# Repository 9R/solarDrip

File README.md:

# SolarDrip

Aim of this project is to create a drop in replacement PCB for low cost solar irrigation systems to allow integration into home automation setups like home-assistant.

## Features

  * solar and usb-c charging
  * basic battery management
  * pump control
  * 2 capacitative sensors (soil & water level)
  * i2c available for additional actors or sensors
  * spare GPIOs

## Hardware

The PCB fits this [solar irrigation system](https://www.aliexpress.com/item/1005006386588305.html). Other, similar systems might be compatible as well. Connecting a pump, 18650 battery and a big enough 6V solar panel should be enough.

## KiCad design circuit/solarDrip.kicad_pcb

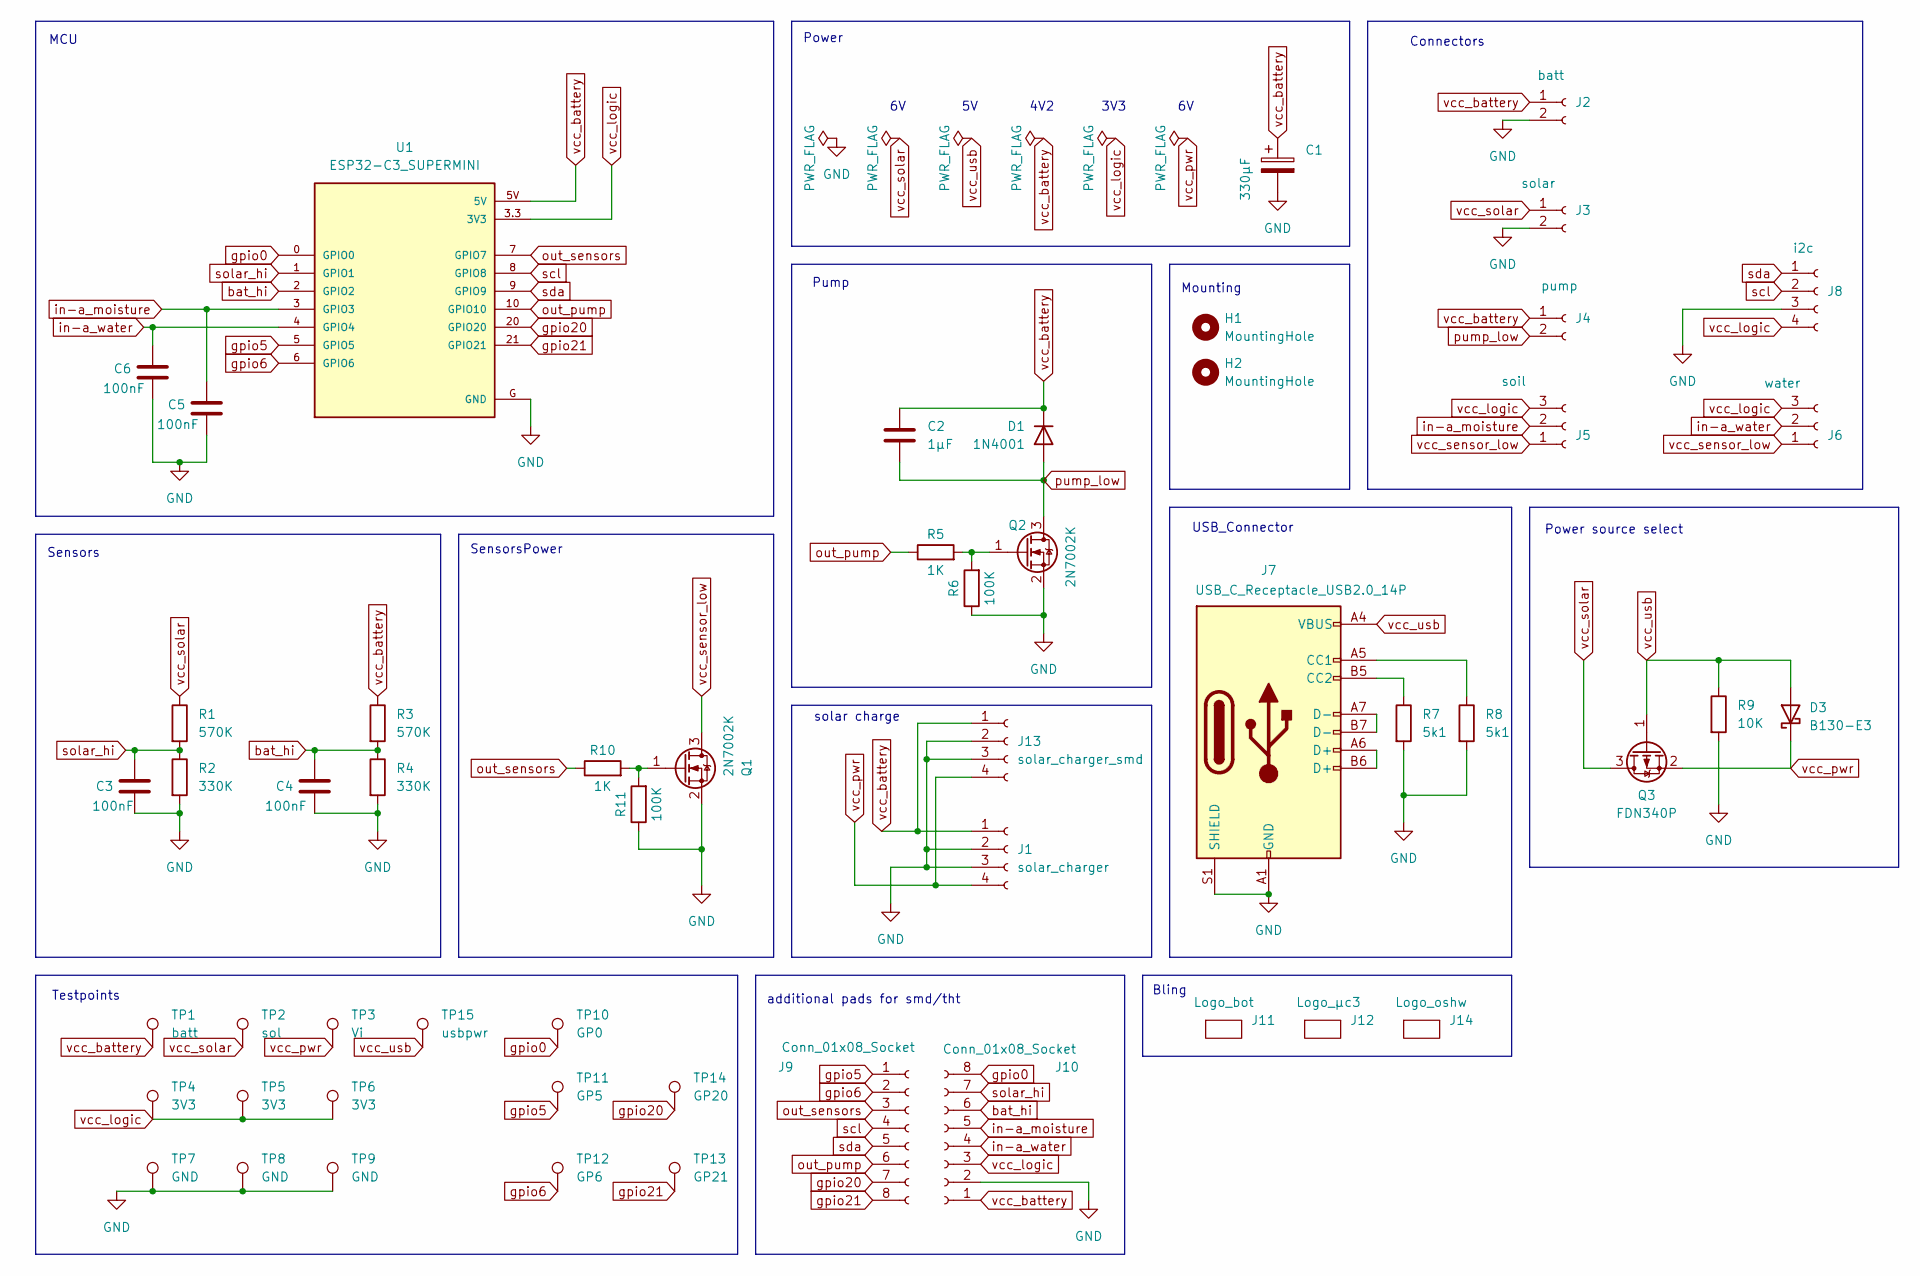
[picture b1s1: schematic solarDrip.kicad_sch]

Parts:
C1: 330µF; CP_Radial_D8.0mm_P3.80mm
C2: 1µF; C_1206_3216Metric_Pad1.33x1.80mm_HandSolder
C3, C4, C5, C6: 100nF; C_0603_1608Metric_Pad1.08x0.95mm_HandSolder
D1: 1N4001; D_SMA-SMB_Universal_Handsoldering
D3: B130-E3; D_SMA
H1, H2: MountingHole; MountingHole_2.7mm_M2.5_DIN965
J1: solar_charger; PinSocket_1x04_P2.54mm_Vertical
J2: batt; JST_PH_S2B-PH-K_1x02_P2.00mm_Horizontal
J3: solar; JST_PH_S2B-PH-K_1x02_P2.00mm_Horizontal
J4: pump; JST_PH_S2B-PH-K_1x02_P2.00mm_Horizontal
J5: soil; JST_PH_S3B-PH-K_1x03_P2.00mm_Horizontal
J6: water; JST_PH_S3B-PH-K_1x03_P2.00mm_Horizontal
J7: USB_C_Receptacle_USB2.0_14P; USB_C_Receptacle_G-Switch_GT-USB-7010ASV
J8: i2c; JST_PH_S4B-PH-K_1x04_P2.00mm_Horizontal
J9, J10: Conn_01x08_Socket; PinSocket_1x08_P2.54mm_Vertical_SMD_Pin1Left
J11: Logo_bot; logo_solardrip
J12: Logo_µc3; muccc_logo
J13: solar_charger_smd; PinSocket_1x04_P2.54mm_Vertical_SMD_Pin1Left
J14: Logo_oshw; OSHW-Logo_5.7x6mm_SilkScreen
Q1, Q2: 2N7002K; SOT-23
Q3: FDN340P; SOT-23
R1, R3: 570K; R_0603_1608Metric_Pad0.98x0.95mm_HandSolder
R2, R4: 330K; R_0603_1608Metric_Pad0.98x0.95mm_HandSolder
R5, R10: 1K; R_0603_1608Metric_Pad0.98x0.95mm_HandSolder
R6, R11: 100K; R_0603_1608Metric_Pad0.98x0.95mm_HandSolder
R7, R8: 5k1; R_0603_1608Metric_Pad0.98x0.95mm_HandSolder
R9: 10K; R_0603_1608Metric_Pad0.98x0.95mm_HandSolder
TP1: batt; TestPoint_Pad_D2.0mm
TP2: sol; TestPoint_Pad_D2.0mm
TP3: Vi; TestPoint_Pad_D2.0mm
TP4, TP5, TP6: 3V3; TestPoint_Pad_D2.0mm
TP7, TP8, TP9: GND; TestPoint_Pad_2.0x2.0mm
TP10: GP0; TestPoint_Pad_D2.0mm
TP11: GP5; TestPoint_Pad_D2.0mm
TP12: GP6; TestPoint_Pad_D2.0mm
TP13: GP21; TestPoint_Pad_D2.0mm
TP14: GP20; TestPoint_Pad_D2.0mm
TP15: usbpwr; TestPoint_Pad_D2.0mm
U1: ESP32-C3_SUPERMINI; MODULE_ESP32-C3_SUPERMINI

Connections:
GND: C1.2, C3.2, C4.2, C5.2, C6.2, J1.2, J1.3, J2.2, J3.2, J7.A1 (GND), J7.A12 (GND), J7.B1 (GND), J7.B12 (GND), J7.S1 (SHIELD), J8.3, J10.2, J13.2, J13.3, Q1.2 (S), Q2.2 (S), R2.2, R4.2, R6.1, R7.2, R8.2, R9.2, R11.1, TP7.1, TP8.1, TP9.1, U1.G (GND)
unnamed: J7.A5 (CC1), R8.1
unnamed: J7.B5 (CC2), R7.1
unnamed: J7.A6 (D+), J7.B6 (D+)
unnamed: J7.A7 (D-), J7.B7 (D-)
unnamed: Q1.1 (G), R10.2, R11.2
unnamed: Q2.1 (G), R5.2, R6.2
bat_hi: C4.1, J10.6, R3.2, R4.1, U1.2 (GPIO2)
gpio0: J10.8, TP10.1, U1.0 (GPIO0)
gpio5: J9.1, TP11.1, U1.5 (GPIO5)
gpio6: J9.2, TP12.1, U1.6 (GPIO6)
gpio20: J9.7, TP14.1, U1.20 (GPIO20)
gpio21: J9.8, TP13.1, U1.21 (GPIO21)
in-a_moisture: C5.1, J5.2, J10.5, U1.3 (GPIO3)
in-a_water: C6.1, J6.2, J10.4, U1.4 (GPIO4)
out_pump: J9.6, R5.1, U1.10 (GPIO10)
out_sensors: J9.3, R10.1, U1.7 (GPIO7)
pump_low: C2.2, D1.2 (A), J4.2, Q2.3 (D)
scl: J8.2, J9.4, U1.8 (GPIO8)
sda: J8.1, J9.5, U1.9 (GPIO9)
solar_hi: C3.1, J10.7, R1.2, R2.1, U1.1 (GPIO1)
vcc_battery: C1.1, C2.1, D1.1 (K), J1.1, J2.1, J4.1, J10.1, J13.1, R3.1, TP1.1, U1.5V
vcc_logic: J5.3, J6.3, J8.4, J10.3, TP4.1, TP5.1, TP6.1, U1.3.3 (3V3)
vcc_pwr: D3.1 (K), J1.4, J13.4, Q3.2 (S), TP3.1
vcc_sensor_low: J5.1, J6.1, Q1.3 (D)
vcc_solar: J3.1, Q3.3 (D), R1.1, TP2.1
vcc_usb: D3.2 (A), J7.A4 (VBUS), J7.A9 (VBUS), J7.B4 (VBUS), J7.B9 (VBUS), Q3.1 (G), R9.1, TP15.1

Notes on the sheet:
Power source select
Bling
Mounting
3V3
MCU
SensorsPower
Connectors
USB_Connector
solar charge
4V2
Testpoints
Pump
Power
additional pads for smd/tht
Sensors

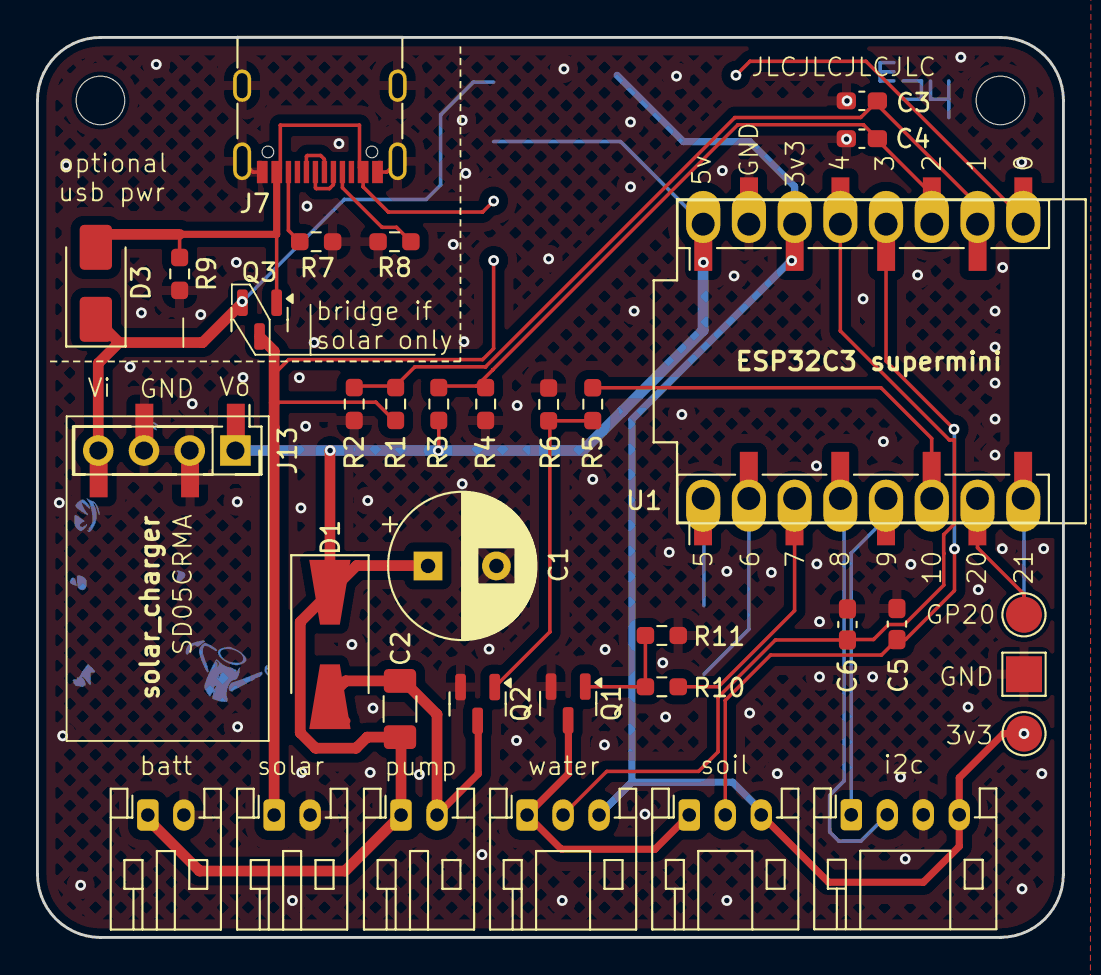
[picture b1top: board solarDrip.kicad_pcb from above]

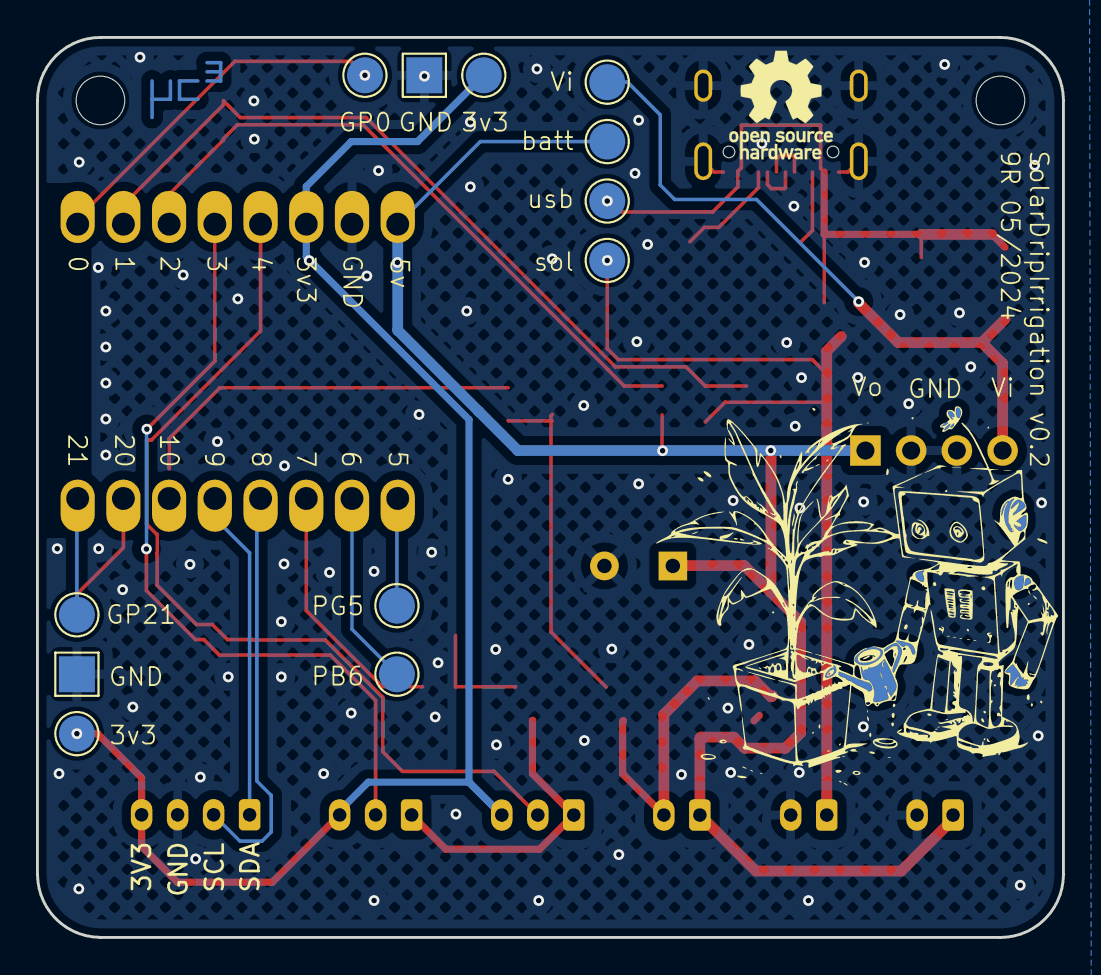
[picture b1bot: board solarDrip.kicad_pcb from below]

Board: 2 copper layers, 57.0 x 50.0 mm, 54 parts (15 on the bottom side), 27 nets.

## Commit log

2024-05-01 init
2024-05-01 add mechanical model
2024-05-01 add pcb to mechanical model
2024-05-01 prepare pcb for edge import
2024-05-01 add gitignore
2024-05-03 add usb charging source
2024-05-03 cleanup and annotations
2024-05-03 replace usb_connector
2024-05-03 various updates
2024-05-03 add esp32c3 supermini 3d model
2024-05-03 update pcb model
2024-05-08 add s annotations
2024-05-09 add datasheets
2024-05-09 init supermini variant
2024-05-09 add usb_charging
2024-05-09 add power select circuit
2024-05-09 first stab at pcb placement
2024-05-09 routing done
2024-05-09 run drc
2024-05-09 add testpoints & i2c to scematics
2024-05-09 vias, silkscreen, add usb_prw, logos and serials
2024-05-09 flip usb and testpoint sides
2024-05-09 add capacitor, cleanup
2024-05-10 move usb_pwr parts around
2024-05-10 move more stuff around
2024-05-10 artwork: init
2024-05-10 add motor cap
2024-05-14 add additional pads for smd/tht sockets
2024-05-14 pcb: add U1 smd pads
2024-05-14 sch: add bypass caps to sensor pins
2024-05-14 add sensor pypass caps
2024-05-14 add artwork: dripbot & mc3 logo
2024-05-19 add knockout fonts
2024-05-19 update mechanical model
2024-05-19 add hatched fill
2024-05-20 check vias
2024-05-20 resize R1-R4 to 0306
2024-05-20 resize R5-R9 to 0306
2024-05-20 add logo symbols
2024-05-20 fix usb net
2024-05-20 add OSHW logo
2024-05-20 small improvements
2024-05-20 change caps to 0603
2024-05-22 set resistor values, schematic cleanup
2024-05-24 set R values
2024-05-26 minor postioning adjustments
2024-06-12 v0.1 production layout
2024-06-12 add ibom
2024-06-26 add README
